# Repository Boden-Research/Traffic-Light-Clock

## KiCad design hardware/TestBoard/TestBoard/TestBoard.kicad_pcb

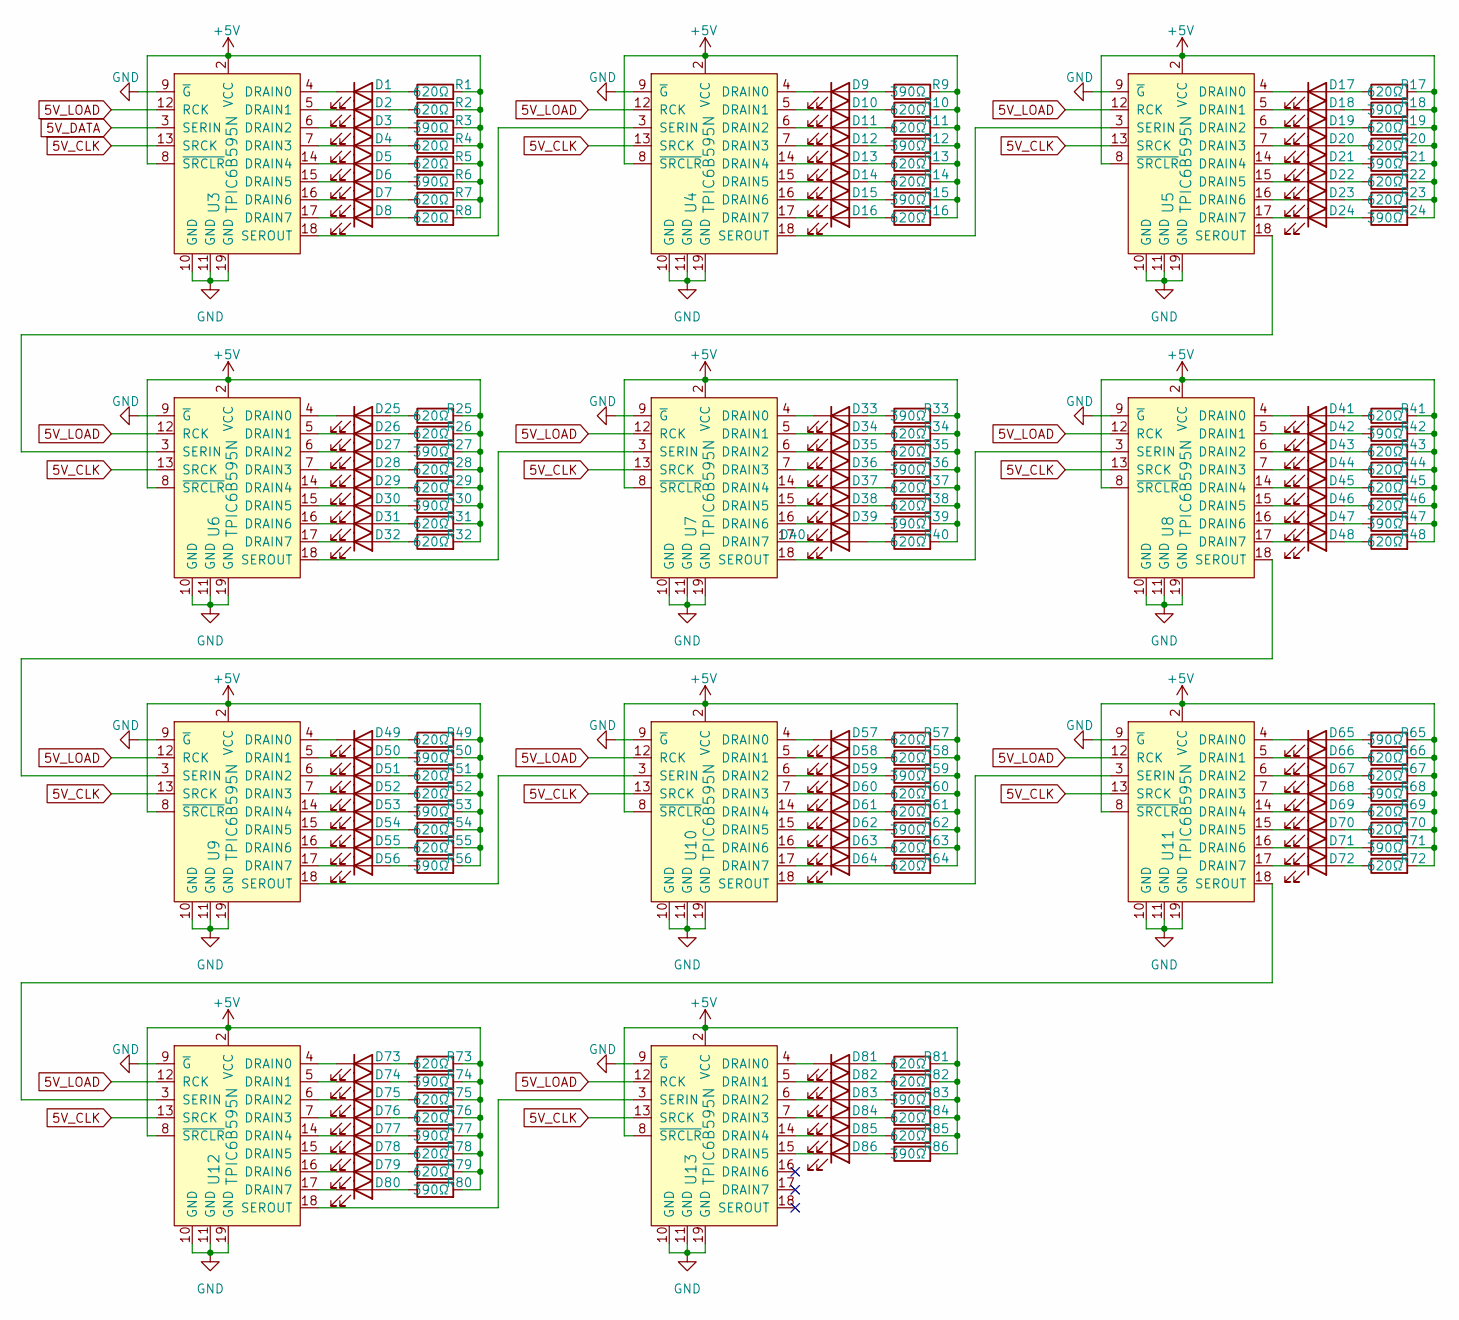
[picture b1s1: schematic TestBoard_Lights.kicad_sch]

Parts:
D1, D4, D7, D10, D13, D16, D19, D22, D25, D28, D31, D34, D37, D40, D45, D48, D51, D54, D57, D60, D63, D66, D69, D72, D75, D78, D81, D84: R; LED_0402_1005Metric; LCSC Part # C52675960
D2, D5, D8, D11, D14, D17, D20, D23, D26, D29, D32, D35, D38, D41, D43, D44, D46, D49, D52, D55, D58, D61, D64, D67, D70, D73, D76, D79, D82, D85: Y; LED_0402_1005Metric; LCSC Part # C52675964
D3, D6, D9, D12, D15, D18, D21, D24, D27, D30, D33, D36, D39, D42, D47, D50, D53, D56, D59, D62, D65, D68, D71, D74, D77, D80, D83, D86: G; LED_0402_1005Metric; LCSC Part # C52675961
R1, R2, R4, R5, R7, R8, R10, R11, R13, R14, R16, R17, R19, R20, R22, R23, R25, R26, R28, R29, R31, R32, R34, R35, R37, R38, R40, R41, R43, R44, R45, R46, R48, R49, R51, R52, R54, R55, R57, R58, R60, R61, R63, R64, R66, R67, R69, R70, R72, R73, R75, R76, R78, R79, R81, R82, R84, R85: 620Ω; R_0402_1005Metric; LCSC Part # C137951
R3, R6, R9, R12, R15, R18, R21, R24, R27, R30, R33, R36, R39, R42, R47, R50, R53, R56, R59, R62, R65, R68, R71, R74, R77, R80, R83, R86: 390Ω; R_0402_1005Metric; LCSC Part # C137997
U3, U4, U5, U6, U7, U8, U9, U10, U11, U12, U13: TPIC6B595N; MPN TPIC6B595N; Digi-Key_PN 296-1956-5-ND

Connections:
5V_CLK: U3.13 (SRCK), U4.13 (SRCK), U5.13 (SRCK), U6.13 (SRCK), U7.13 (SRCK), U8.13 (SRCK), U9.13 (SRCK), U10.13 (SRCK), U11.13 (SRCK), U12.13 (SRCK), U13.13 (SRCK); also elsewhere on the board
5V_DATA: U3.3 (SERIN); also elsewhere on the board
5V_LOAD: U3.12 (RCK), U4.12 (RCK), U5.12 (RCK), U6.12 (RCK), U7.12 (RCK), U8.12 (RCK), U9.12 (RCK), U10.12 (RCK), U11.12 (RCK), U12.12 (RCK), U13.12 (RCK); also elsewhere on the board
+5V: R1.2, R2.2, R3.2, R4.2, R5.2, R6.2, R7.2, R8.2, R9.2, R10.2, R11.2, R12.2, R13.2, R14.2, R15.2, R16.2, R17.2, R18.2, R19.2, R20.2, R21.2, R22.2, R23.2, R24.2, R25.2, R26.2, R27.2, R28.2, R29.2, R30.2, R31.2, R32.2, R33.2, R34.2, R35.2, R36.2, R37.2, R38.2, R39.2, R40.2, R41.2, R42.2, R43.2, R44.2, R45.2, R46.2, R47.2, R48.2, R49.2, R50.2, R51.2, R52.2, R53.2, R54.2, R55.2, R56.2, R57.2, R58.2, R59.2, R60.2, R61.2, R62.2, R63.2, R64.2, R65.2, R66.2, R67.2, R68.2, R69.2, R70.2, R71.2, R72.2, R73.2, R74.2, R75.2, R76.2, R77.2, R78.2, R79.2, R80.2, R81.2, R82.2, R83.2, R84.2, R85.2, R86.2, U3.2 (VCC), U3.8 (~SRCLR), U4.2 (VCC), U4.8 (~SRCLR), U5.2 (VCC), U5.8 (~SRCLR), U6.2 (VCC), U6.8 (~SRCLR), U7.2 (VCC), U7.8 (~SRCLR), U8.2 (VCC), U8.8 (~SRCLR), U9.2 (VCC), U9.8 (~SRCLR), U10.2 (VCC), U10.8 (~SRCLR), U11.2 (VCC), U11.8 (~SRCLR), U12.2 (VCC), U12.8 (~SRCLR), U13.2 (VCC), U13.8 (~SRCLR); also elsewhere on the board
GND: U3.9 (~G), U3.10 (GND), U3.11 (GND), U3.19 (GND), U4.9 (~G), U4.10 (GND), U4.11 (GND), U4.19 (GND), U5.9 (~G), U5.10 (GND), U5.11 (GND), U5.19 (GND), U6.9 (~G), U6.10 (GND), U6.11 (GND), U6.19 (GND), U7.9 (~G), U7.10 (GND), U7.11 (GND), U7.19 (GND), U8.9 (~G), U8.10 (GND), U8.11 (GND), U8.19 (GND), U9.9 (~G), U9.10 (GND), U9.11 (GND), U9.19 (GND), U10.9 (~G), U10.10 (GND), U10.11 (GND), U10.19 (GND), U11.9 (~G), U11.10 (GND), U11.11 (GND), U11.19 (GND), U12.9 (~G), U12.10 (GND), U12.11 (GND), U12.19 (GND), U13.9 (~G), U13.10 (GND), U13.11 (GND), U13.19 (GND); also elsewhere on the board
unnamed: D1.2 (A), R1.1
unnamed: D1.1 (K), U3.4 (DRAIN0)
unnamed: D2.2 (A), R2.1
unnamed: D2.1 (K), U3.5 (DRAIN1)
unnamed: D3.2 (A), R3.1
unnamed: D3.1 (K), U3.6 (DRAIN2)
unnamed: D4.2 (A), R4.1
unnamed: D4.1 (K), U3.7 (DRAIN3)
unnamed: D5.2 (A), R5.1
unnamed: D5.1 (K), U3.14 (DRAIN4)
unnamed: D6.2 (A), R6.1
unnamed: D6.1 (K), U3.15 (DRAIN5)
unnamed: D7.2 (A), R7.1
unnamed: D7.1 (K), U3.16 (DRAIN6)
unnamed: D8.2 (A), R8.1
unnamed: D8.1 (K), U3.17 (DRAIN7)
unnamed: D9.2 (A), R9.1
unnamed: D9.1 (K), U4.4 (DRAIN0)
unnamed: D10.2 (A), R10.1
unnamed: D10.1 (K), U4.5 (DRAIN1)
unnamed: D11.2 (A), R11.1
unnamed: D11.1 (K), U4.6 (DRAIN2)
unnamed: D12.2 (A), R12.1
unnamed: D12.1 (K), U4.7 (DRAIN3)
unnamed: D13.2 (A), R13.1
unnamed: D13.1 (K), U4.14 (DRAIN4)
unnamed: D14.2 (A), R14.1
unnamed: D14.1 (K), U4.15 (DRAIN5)
unnamed: D15.2 (A), R15.1
unnamed: D15.1 (K), U4.16 (DRAIN6)
unnamed: D16.2 (A), R16.1
unnamed: D16.1 (K), U4.17 (DRAIN7)
unnamed: D17.2 (A), R17.1
unnamed: D17.1 (K), U5.4 (DRAIN0)
unnamed: D18.2 (A), R18.1
unnamed: D18.1 (K), U5.5 (DRAIN1)
unnamed: D19.2 (A), R19.1
unnamed: D19.1 (K), U5.6 (DRAIN2)
unnamed: D20.2 (A), R20.1
unnamed: D20.1 (K), U5.7 (DRAIN3)
unnamed: D21.2 (A), R21.1
unnamed: D21.1 (K), U5.14 (DRAIN4)
unnamed: D22.2 (A), R22.1
unnamed: D22.1 (K), U5.15 (DRAIN5)
unnamed: D23.2 (A), R23.1
unnamed: D23.1 (K), U5.16 (DRAIN6)
unnamed: D24.2 (A), R24.1
unnamed: D24.1 (K), U5.17 (DRAIN7)
unnamed: D25.2 (A), R25.1
unnamed: D25.1 (K), U6.4 (DRAIN0)
unnamed: D26.2 (A), R26.1
unnamed: D26.1 (K), U6.5 (DRAIN1)
unnamed: D27.2 (A), R27.1
unnamed: D27.1 (K), U6.6 (DRAIN2)
unnamed: D28.2 (A), R28.1
unnamed: D28.1 (K), U6.7 (DRAIN3)
unnamed: D29.2 (A), R29.1
unnamed: D29.1 (K), U6.14 (DRAIN4)
unnamed: D30.2 (A), R30.1
unnamed: D30.1 (K), U6.15 (DRAIN5)
unnamed: D31.2 (A), R31.1
unnamed: D31.1 (K), U6.16 (DRAIN6)
unnamed: D32.2 (A), R32.1
unnamed: D32.1 (K), U6.17 (DRAIN7)
unnamed: D33.2 (A), R33.1
unnamed: D33.1 (K), U7.4 (DRAIN0)
unnamed: D34.2 (A), R34.1
unnamed: D34.1 (K), U7.5 (DRAIN1)
unnamed: D35.2 (A), R35.1
unnamed: D35.1 (K), U7.6 (DRAIN2)
unnamed: D36.2 (A), R36.1
unnamed: D36.1 (K), U7.7 (DRAIN3)
unnamed: D37.2 (A), R37.1
unnamed: D37.1 (K), U7.14 (DRAIN4)
unnamed: D38.2 (A), R38.1
unnamed: D38.1 (K), U7.15 (DRAIN5)
unnamed: D39.2 (A), R39.1
unnamed: D39.1 (K), U7.16 (DRAIN6)
unnamed: D40.2 (A), R40.1
unnamed: D40.1 (K), U7.17 (DRAIN7)
unnamed: D41.2 (A), R41.1
unnamed: D41.1 (K), U8.4 (DRAIN0)
unnamed: D42.2 (A), R42.1
unnamed: D42.1 (K), U8.5 (DRAIN1)
unnamed: D43.2 (A), R43.1
unnamed: D43.1 (K), U8.6 (DRAIN2)
unnamed: D44.2 (A), R44.1
unnamed: D44.1 (K), U8.7 (DRAIN3)
unnamed: D45.2 (A), R45.1
unnamed: D45.1 (K), U8.14 (DRAIN4)
unnamed: D46.2 (A), R46.1
unnamed: D46.1 (K), U8.15 (DRAIN5)
unnamed: D47.2 (A), R47.1
unnamed: D47.1 (K), U8.16 (DRAIN6)
unnamed: D48.2 (A), R48.1
unnamed: D48.1 (K), U8.17 (DRAIN7)
unnamed: D49.2 (A), R49.1
unnamed: D49.1 (K), U9.4 (DRAIN0)
unnamed: D50.2 (A), R50.1
unnamed: D50.1 (K), U9.5 (DRAIN1)
unnamed: D51.2 (A), R51.1
unnamed: D51.1 (K), U9.6 (DRAIN2)
unnamed: D52.2 (A), R52.1
unnamed: D52.1 (K), U9.7 (DRAIN3)
unnamed: D53.2 (A), R53.1
unnamed: D53.1 (K), U9.14 (DRAIN4)
unnamed: D54.2 (A), R54.1
unnamed: D54.1 (K), U9.15 (DRAIN5)
unnamed: D55.2 (A), R55.1
unnamed: D55.1 (K), U9.16 (DRAIN6)
unnamed: D56.2 (A), R56.1
unnamed: D56.1 (K), U9.17 (DRAIN7)
unnamed: D57.2 (A), R57.1
unnamed: D57.1 (K), U10.4 (DRAIN0)
unnamed: D58.2 (A), R58.1
unnamed: D58.1 (K), U10.5 (DRAIN1)
unnamed: D59.2 (A), R59.1
unnamed: D59.1 (K), U10.6 (DRAIN2)
unnamed: D60.2 (A), R60.1
unnamed: D60.1 (K), U10.7 (DRAIN3)
unnamed: D61.2 (A), R61.1
unnamed: D61.1 (K), U10.14 (DRAIN4)
unnamed: D62.2 (A), R62.1
unnamed: D62.1 (K), U10.15 (DRAIN5)
unnamed: D63.2 (A), R63.1
unnamed: D63.1 (K), U10.16 (DRAIN6)
unnamed: D64.2 (A), R64.1
unnamed: D64.1 (K), U10.17 (DRAIN7)
unnamed: D65.2 (A), R65.1
unnamed: D65.1 (K), U11.4 (DRAIN0)
unnamed: D66.2 (A), R66.1
unnamed: D66.1 (K), U11.5 (DRAIN1)
unnamed: D67.2 (A), R67.1
unnamed: D67.1 (K), U11.6 (DRAIN2)
unnamed: D68.2 (A), R68.1
unnamed: D68.1 (K), U11.7 (DRAIN3)
unnamed: D69.2 (A), R69.1
unnamed: D69.1 (K), U11.14 (DRAIN4)
unnamed: D70.2 (A), R70.1
unnamed: D70.1 (K), U11.15 (DRAIN5)
unnamed: D71.2 (A), R71.1
unnamed: D71.1 (K), U11.16 (DRAIN6)
unnamed: D72.2 (A), R72.1
unnamed: D72.1 (K), U11.17 (DRAIN7)
unnamed: D73.2 (A), R73.1
unnamed: D73.1 (K), U12.4 (DRAIN0)
unnamed: D74.2 (A), R74.1
unnamed: D74.1 (K), U12.5 (DRAIN1)
unnamed: D75.2 (A), R75.1
unnamed: D75.1 (K), U12.6 (DRAIN2)
unnamed: D76.2 (A), R76.1
unnamed: D76.1 (K), U12.7 (DRAIN3)
unnamed: D77.2 (A), R77.1
unnamed: D77.1 (K), U12.14 (DRAIN4)
unnamed: D78.2 (A), R78.1
unnamed: D78.1 (K), U12.15 (DRAIN5)
unnamed: D79.2 (A), R79.1
unnamed: D79.1 (K), U12.16 (DRAIN6)
unnamed: D80.2 (A), R80.1
unnamed: D80.1 (K), U12.17 (DRAIN7)
unnamed: D81.2 (A), R81.1
unnamed: D81.1 (K), U13.4 (DRAIN0)
unnamed: D82.2 (A), R82.1
unnamed: D82.1 (K), U13.5 (DRAIN1)
unnamed: D83.2 (A), R83.1
unnamed: D83.1 (K), U13.6 (DRAIN2)
unnamed: D84.2 (A), R84.1
unnamed: D84.1 (K), U13.7 (DRAIN3)
unnamed: D85.2 (A), R85.1
unnamed: D85.1 (K), U13.14 (DRAIN4)
unnamed: D86.2 (A), R86.1
unnamed: D86.1 (K), U13.15 (DRAIN5)
unnamed: U3.18 (SEROUT), U4.3 (SERIN)
unnamed: U4.18 (SEROUT), U5.3 (SERIN)
unnamed: U5.18 (SEROUT), U6.3 (SERIN)
unnamed: U6.18 (SEROUT), U7.3 (SERIN)
unnamed: U7.18 (SEROUT), U8.3 (SERIN)
unnamed: U8.18 (SEROUT), U9.3 (SERIN)
unnamed: U9.18 (SEROUT), U10.3 (SERIN)
unnamed: U10.18 (SEROUT), U11.3 (SERIN)
unnamed: U11.18 (SEROUT), U12.3 (SERIN)
unnamed: U12.18 (SEROUT), U13.3 (SERIN)

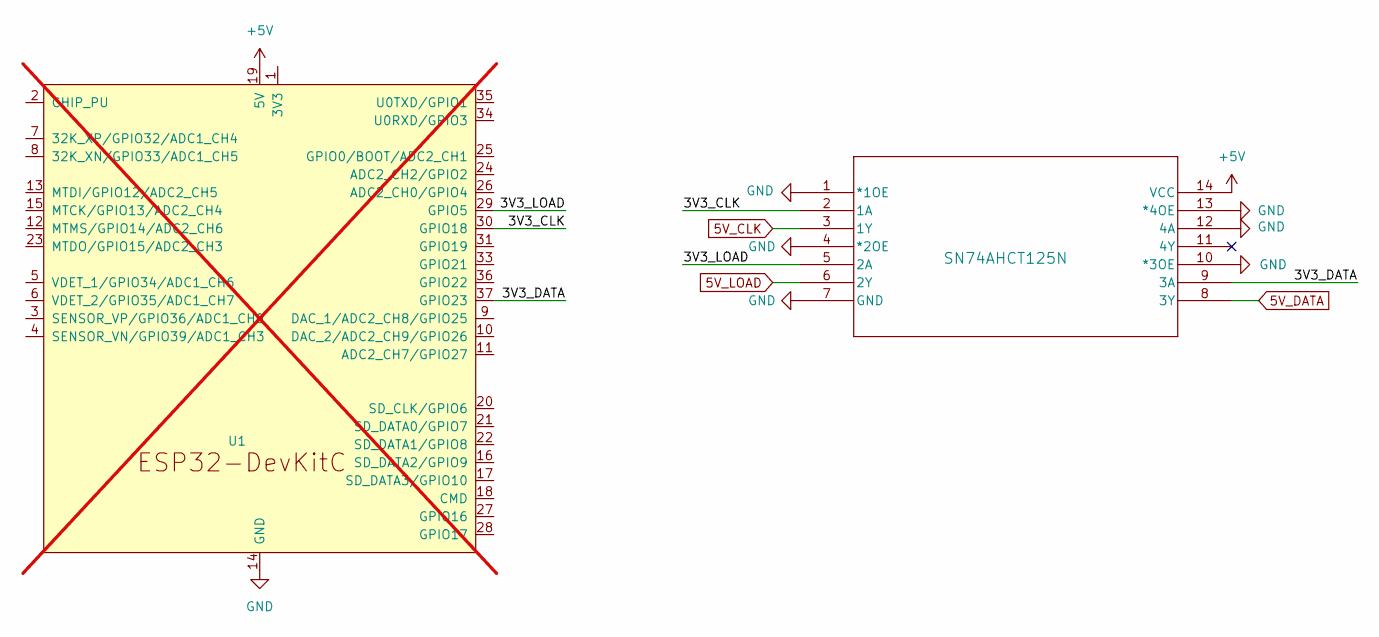
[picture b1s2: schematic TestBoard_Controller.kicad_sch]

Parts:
U1: ESP32-DevKitC; not fitted
U2: SN74AHCT125N; LCSC Part # C154102

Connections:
5V_CLK: U2.3 (1Y); also elsewhere on the board
5V_DATA: U2.8 (3Y); also elsewhere on the board
5V_LOAD: U2.6 (2Y); also elsewhere on the board
+5V: U1.19 (5V), U2.14 (VCC); also elsewhere on the board
/TestBoard_Controller/3V3_CLK: U1.30 (GPIO18), U2.2 (1A)
/TestBoard_Controller/3V3_DATA: U1.37 (GPIO23), U2.9 (3A)
/TestBoard_Controller/3V3_LOAD: U1.29 (GPIO5), U2.5 (2A)
GND: U1.14 (GND), U1.32 (GND), U1.38 (GND), U2.1 (*1OE), U2.4 (*2OE), U2.7 (GND), U2.10 (*3OE), U2.12 (4A), U2.13 (*4OE); also elsewhere on the board

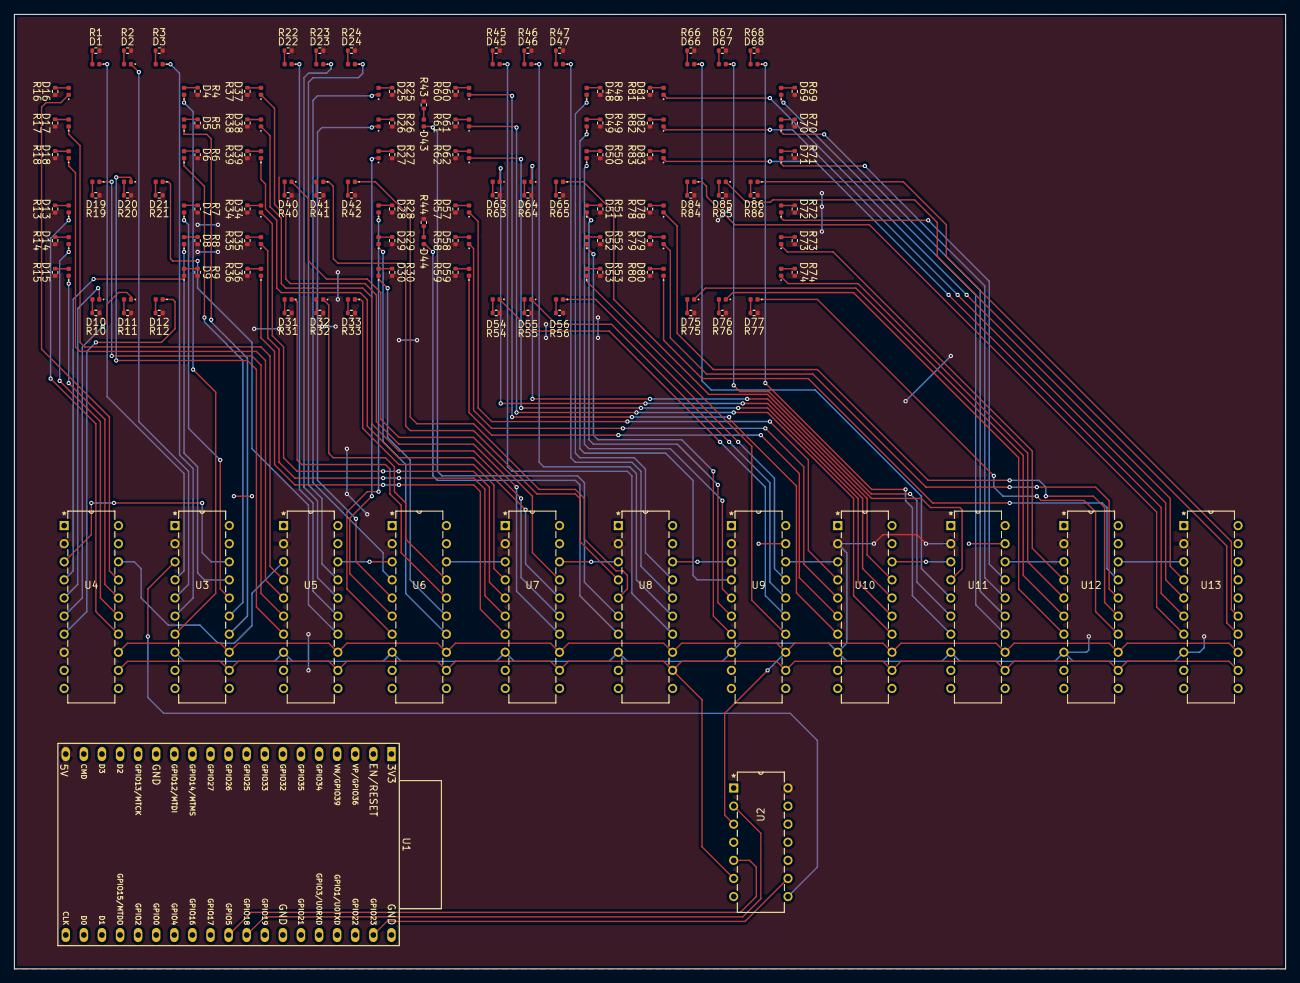
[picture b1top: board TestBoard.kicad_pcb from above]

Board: 2 copper layers, 178.4 x 134.0 mm, 185 parts (0 on the bottom side), 190 nets.

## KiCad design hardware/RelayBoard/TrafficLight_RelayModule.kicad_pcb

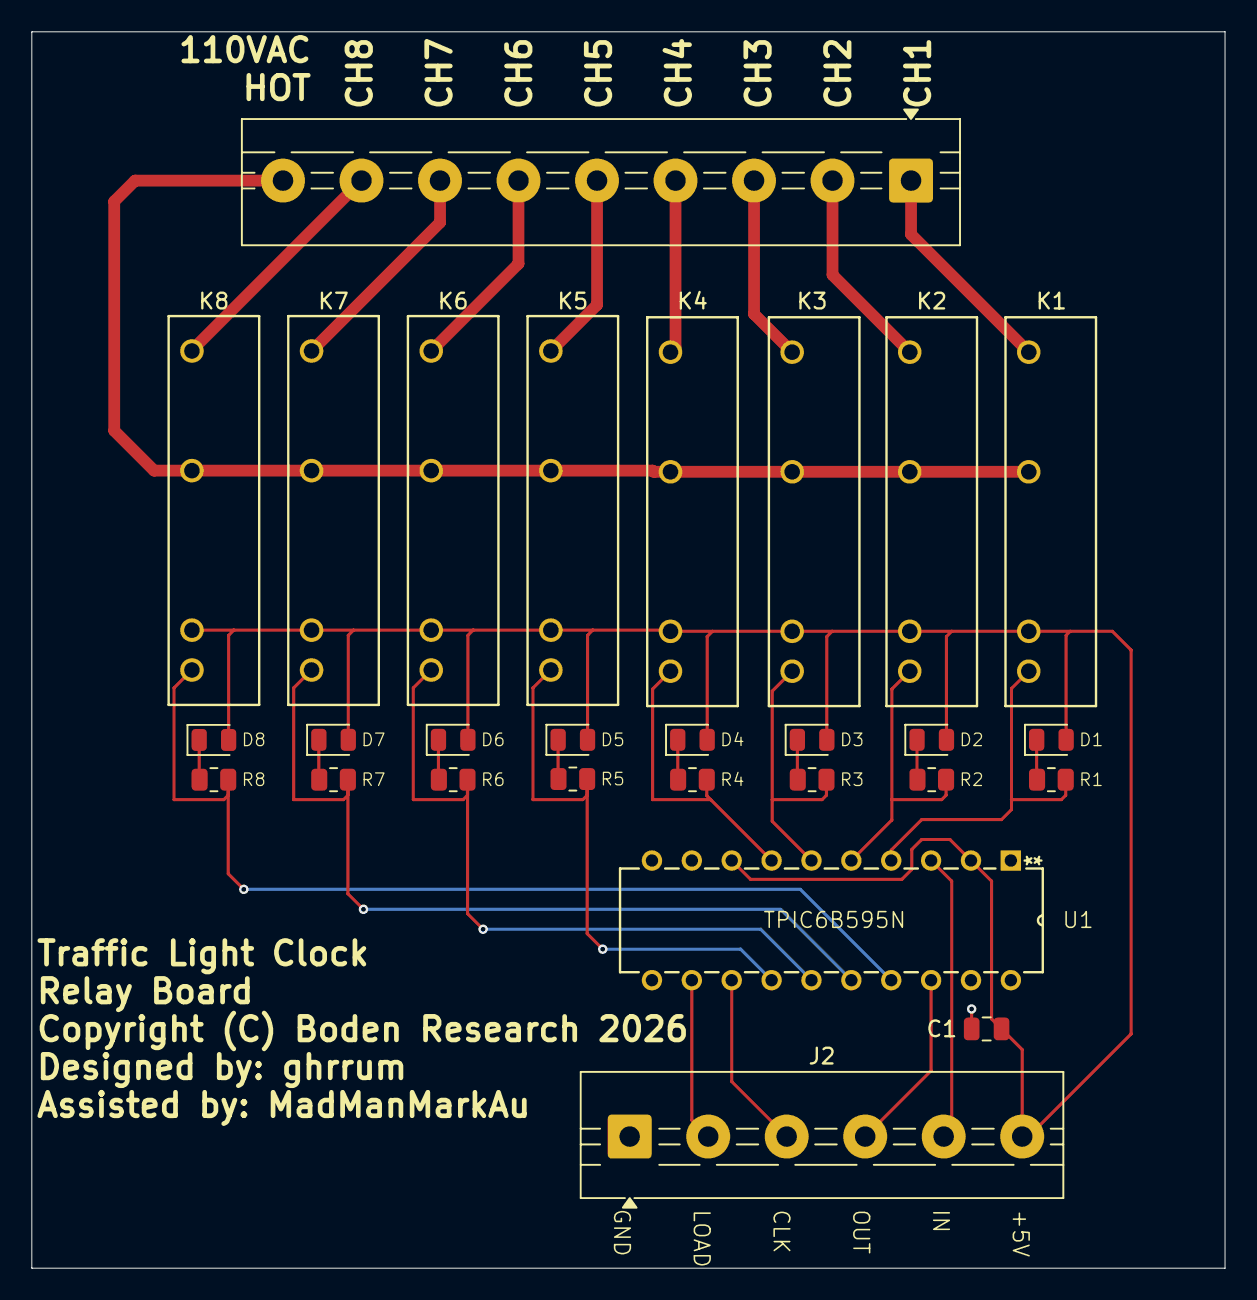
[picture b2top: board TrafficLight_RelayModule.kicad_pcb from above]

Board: 2 copper layers, 76.0 x 78.8 mm, 28 parts (0 on the bottom side), 31 nets.

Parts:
C1: 0.1uF; C_0805_2012Metric
D1, D2, D3, D4, D5, D6, D7, D8: LED; LED_0805_2012Metric
J1: Screw_Terminal_01x09; TerminalBlock_MaiXu_MX126-5.0-09P_1x09_P5.00mm
J2: Screw_Terminal_01x06; TerminalBlock_MaiXu_MX126-5.0-06P_1x06_P5.00mm
K1, K2, K3, K4, K5, K6, K7, K8: G3MB-202P DC5; G3MB_202P_DC5
R1, R2, R3, R4, R5, R6, R7, R8: 1kΩ; R_0805_2012Metric
U1: TPIC6B595N

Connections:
+5V: C1.1, D1.2 (A), D2.2 (A), D3.2 (A), D4.2 (A), D5.2 (A), D6.2 (A), D7.2 (A), D8.2 (A), J2.6, K1.3, K2.3, K3.3, K4.3, K5.3, K6.3, K7.3, K8.3, U1.2 (VCC), U1.8 (~SRCLR)
/110vAC Hawt: J1.9, K1.2, K2.2, K3.2, K4.2, K5.2, K6.2, K7.2, K8.2
GND: C1.2, J2.1, U1.9 (~G), U1.10 (GND), U1.11 (GND), U1.19 (GND)
unnamed: D1.1 (K), R1.1
unnamed: D2.1 (K), R2.1
unnamed: D3.1 (K), R3.1
unnamed: D4.1 (K), R4.1
unnamed: D5.1 (K), R5.1
unnamed: D6.1 (K), R6.1
unnamed: D7.1 (K), R7.1
unnamed: D8.1 (K), R8.1
unnamed: J1.1, K1.1
unnamed: J1.2, K2.1
unnamed: J1.3, K3.1
unnamed: J1.4, K4.1
unnamed: J1.5, K5.1
unnamed: J1.6, K6.1
unnamed: J1.7, K7.1
unnamed: J1.8, K8.1
unnamed: J2.2, U1.12 (RCK)
unnamed: J2.3, U1.13 (SRCK)
unnamed: J2.4, U1.18 (SEROUT)
unnamed: J2.5, U1.3 (SERIN)
unnamed: K1.4, R1.2, U1.4 (DRAIN0)
unnamed: K2.4, R2.2, U1.5 (DRAIN1)
unnamed: K3.4, R3.2, U1.6 (DRAIN2)
unnamed: K4.4, R4.2, U1.7 (DRAIN3)
unnamed: K5.4, R5.2, U1.14 (DRAIN4)
unnamed: K6.4, R6.2, U1.15 (DRAIN5)
unnamed: K7.4, R7.2, U1.16 (DRAIN6)
unnamed: K8.4, R8.2, U1.17 (DRAIN7)

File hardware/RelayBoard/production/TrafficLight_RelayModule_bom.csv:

Designator,Footprint,Quantity,Value,LCSC Part #
C1,0805,1,0.1uF,
"D1, D2, D3, D4, D5, D6, D7, D8",0805,8,LED,
J1,TerminalBlock_MaiXu_MX126-5.0-09P_1x09_P5.00mm,1,Screw_Terminal_01x09,
J2,TerminalBlock_MaiXu_MX126-5.0-06P_1x06_P5.00mm,1,Screw_Terminal_01x06,
"K1, K2, K3, K4, K5, K6, K7, K8",G3MB_202P_DC5,8,G3MB-202P DC5,
"R1, R2, R3, R4, R5, R6, R7, R8",0805,8,1kΩ,
U1,TPIC6B595N,1,TPIC6B595N,TPIC6B595N

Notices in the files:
hardware/RelayBoard/TrafficLight_RelayModule.kicad_pcb:
Copyright (C) Boden Research 2026
